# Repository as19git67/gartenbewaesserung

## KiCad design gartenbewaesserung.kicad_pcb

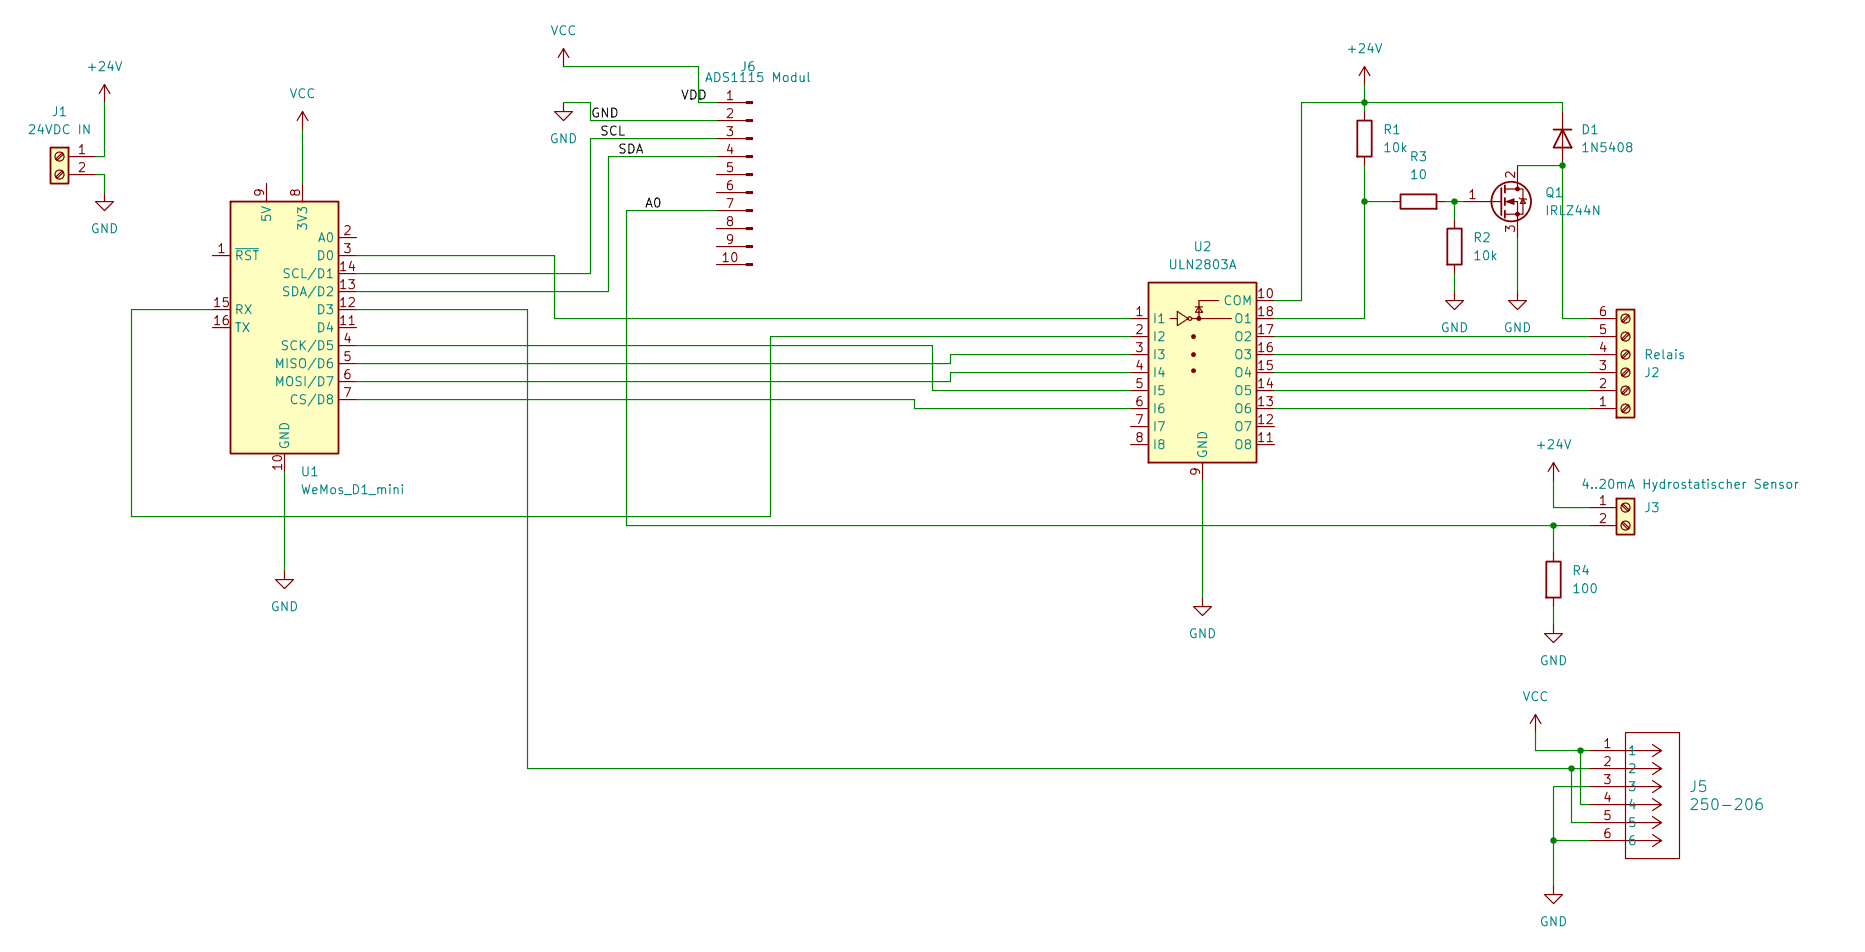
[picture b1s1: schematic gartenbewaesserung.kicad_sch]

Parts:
D1: 1N5408; D_DO-201AD_P15.24mm_Horizontal
J1: 24VDC IN; TerminalBlock_Phoenix_MKDS-3-2-5.08_1x02_P5.08mm_Horizontal
J2: Relais; TerminalBlock_Phoenix_MKDS-3-6-5.08_1x06_P5.08mm_Horizontal
J3: 4..20mA Hydrostatischer Sensor; TerminalBlock_Phoenix_MKDS-3-2-5.08_1x02_P5.08mm_Horizontal
J5: 250-206; CONN_250-206_WAG
J6: ADS1115 Modul; PinHeader_1x10_P2.54mm_Vertical
Q1: IRLZ44N; TO-220-3_Vertical
R1, R2: 10k; R_Axial_DIN0207_L6.3mm_D2.5mm_P7.62mm_Horizontal
R3: 10; R_Axial_DIN0207_L6.3mm_D2.5mm_P7.62mm_Horizontal
R4: 100; R_Axial_DIN0207_L6.3mm_D2.5mm_P7.62mm_Horizontal
U1: WeMos_D1_mini; WEMOS_D1_mini_light
U2: ULN2803A; DIP-18_W7.62mm

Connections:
+24V: D1.1 (K), J1.1, J3.1, R1.1, U2.10 (COM)
/A0: J3.2, J6.7, R4.1
/SCL: J6.3, U1.14 (SCL/D1)
/SDA: J6.4, U1.13 (SDA/D2)
GND: J1.2, J5.3, J5.6, J6.2, Q1.3 (S), R2.2, R4.2, U1.10 (GND), U2.9 (GND)
unnamed: D1.2 (A), J2.6, Q1.2 (D)
unnamed: J2.1, U2.13 (O6)
unnamed: J2.2, U2.14 (O5)
unnamed: J2.3, U2.15 (O4)
unnamed: J2.4, U2.16 (O3)
unnamed: J2.5, U2.17 (O2)
unnamed: Q1.1 (G), R2.1, R3.2
unnamed: U1.7 (CS/D8), U2.6 (I6)
unnamed: U1.3 (D0), U2.1 (I1)
unnamed: J5.2, J5.5, U1.12 (D3)
unnamed: U1.5 (MISO/D6), U2.3 (I3)
unnamed: U1.6 (MOSI/D7), U2.4 (I4)
unnamed: U1.15 (RX), U2.2 (I2)
unnamed: U1.4 (SCK/D5), U2.5 (I5)
unnamed: R1.2, R3.1, U2.18 (O1)
VCC: J5.1, J5.4, J6.1, U1.8 (3V3)

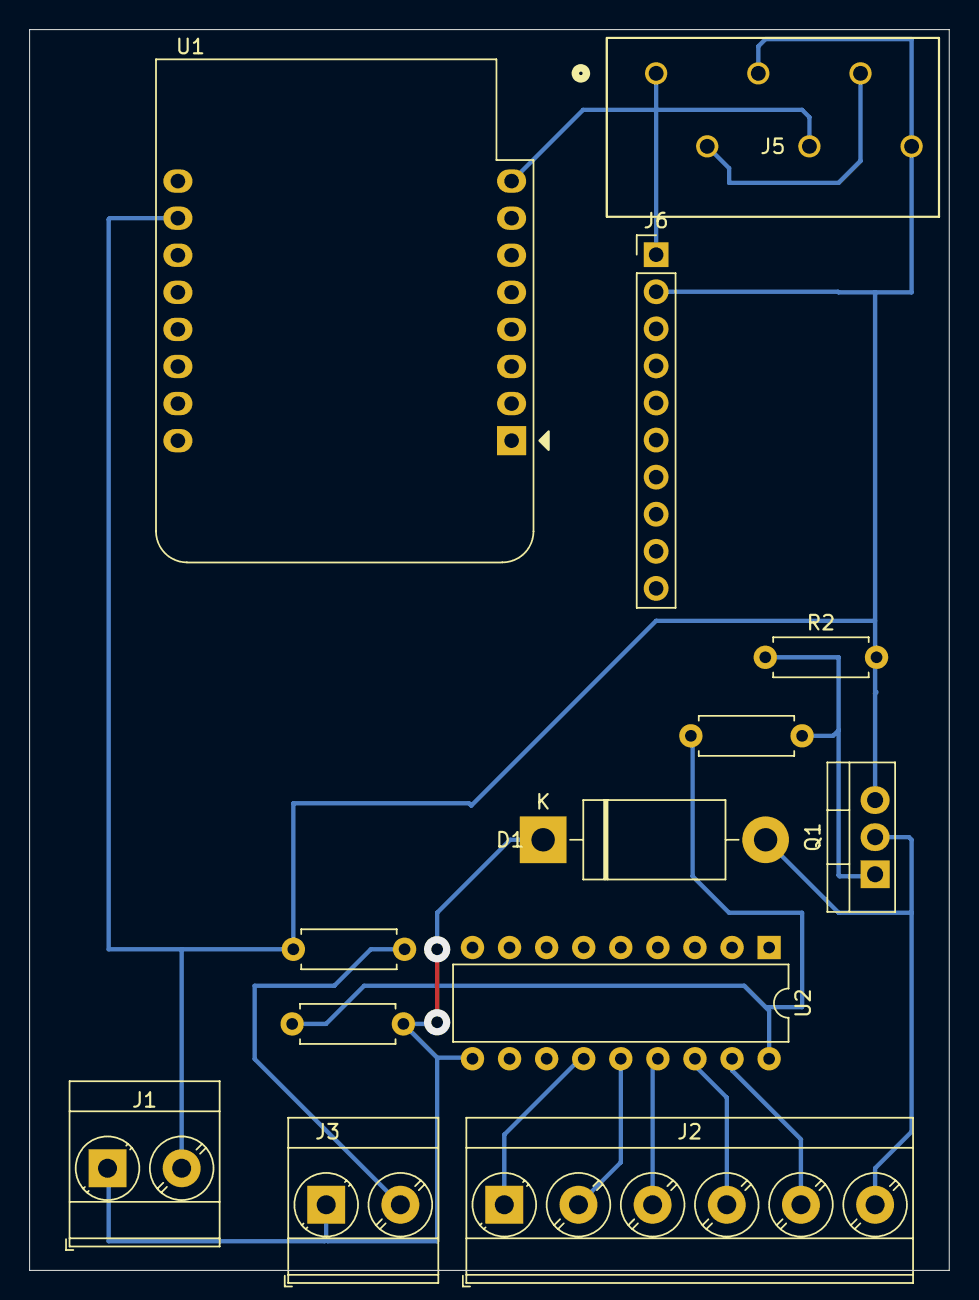
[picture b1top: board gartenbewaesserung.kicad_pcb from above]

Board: 2 copper layers, 63.0 x 85.0 mm, 13 parts (0 on the bottom side), 21 nets.

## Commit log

2024-05-20 initial
2024-05-23 Zustand bei Fertigstellung
